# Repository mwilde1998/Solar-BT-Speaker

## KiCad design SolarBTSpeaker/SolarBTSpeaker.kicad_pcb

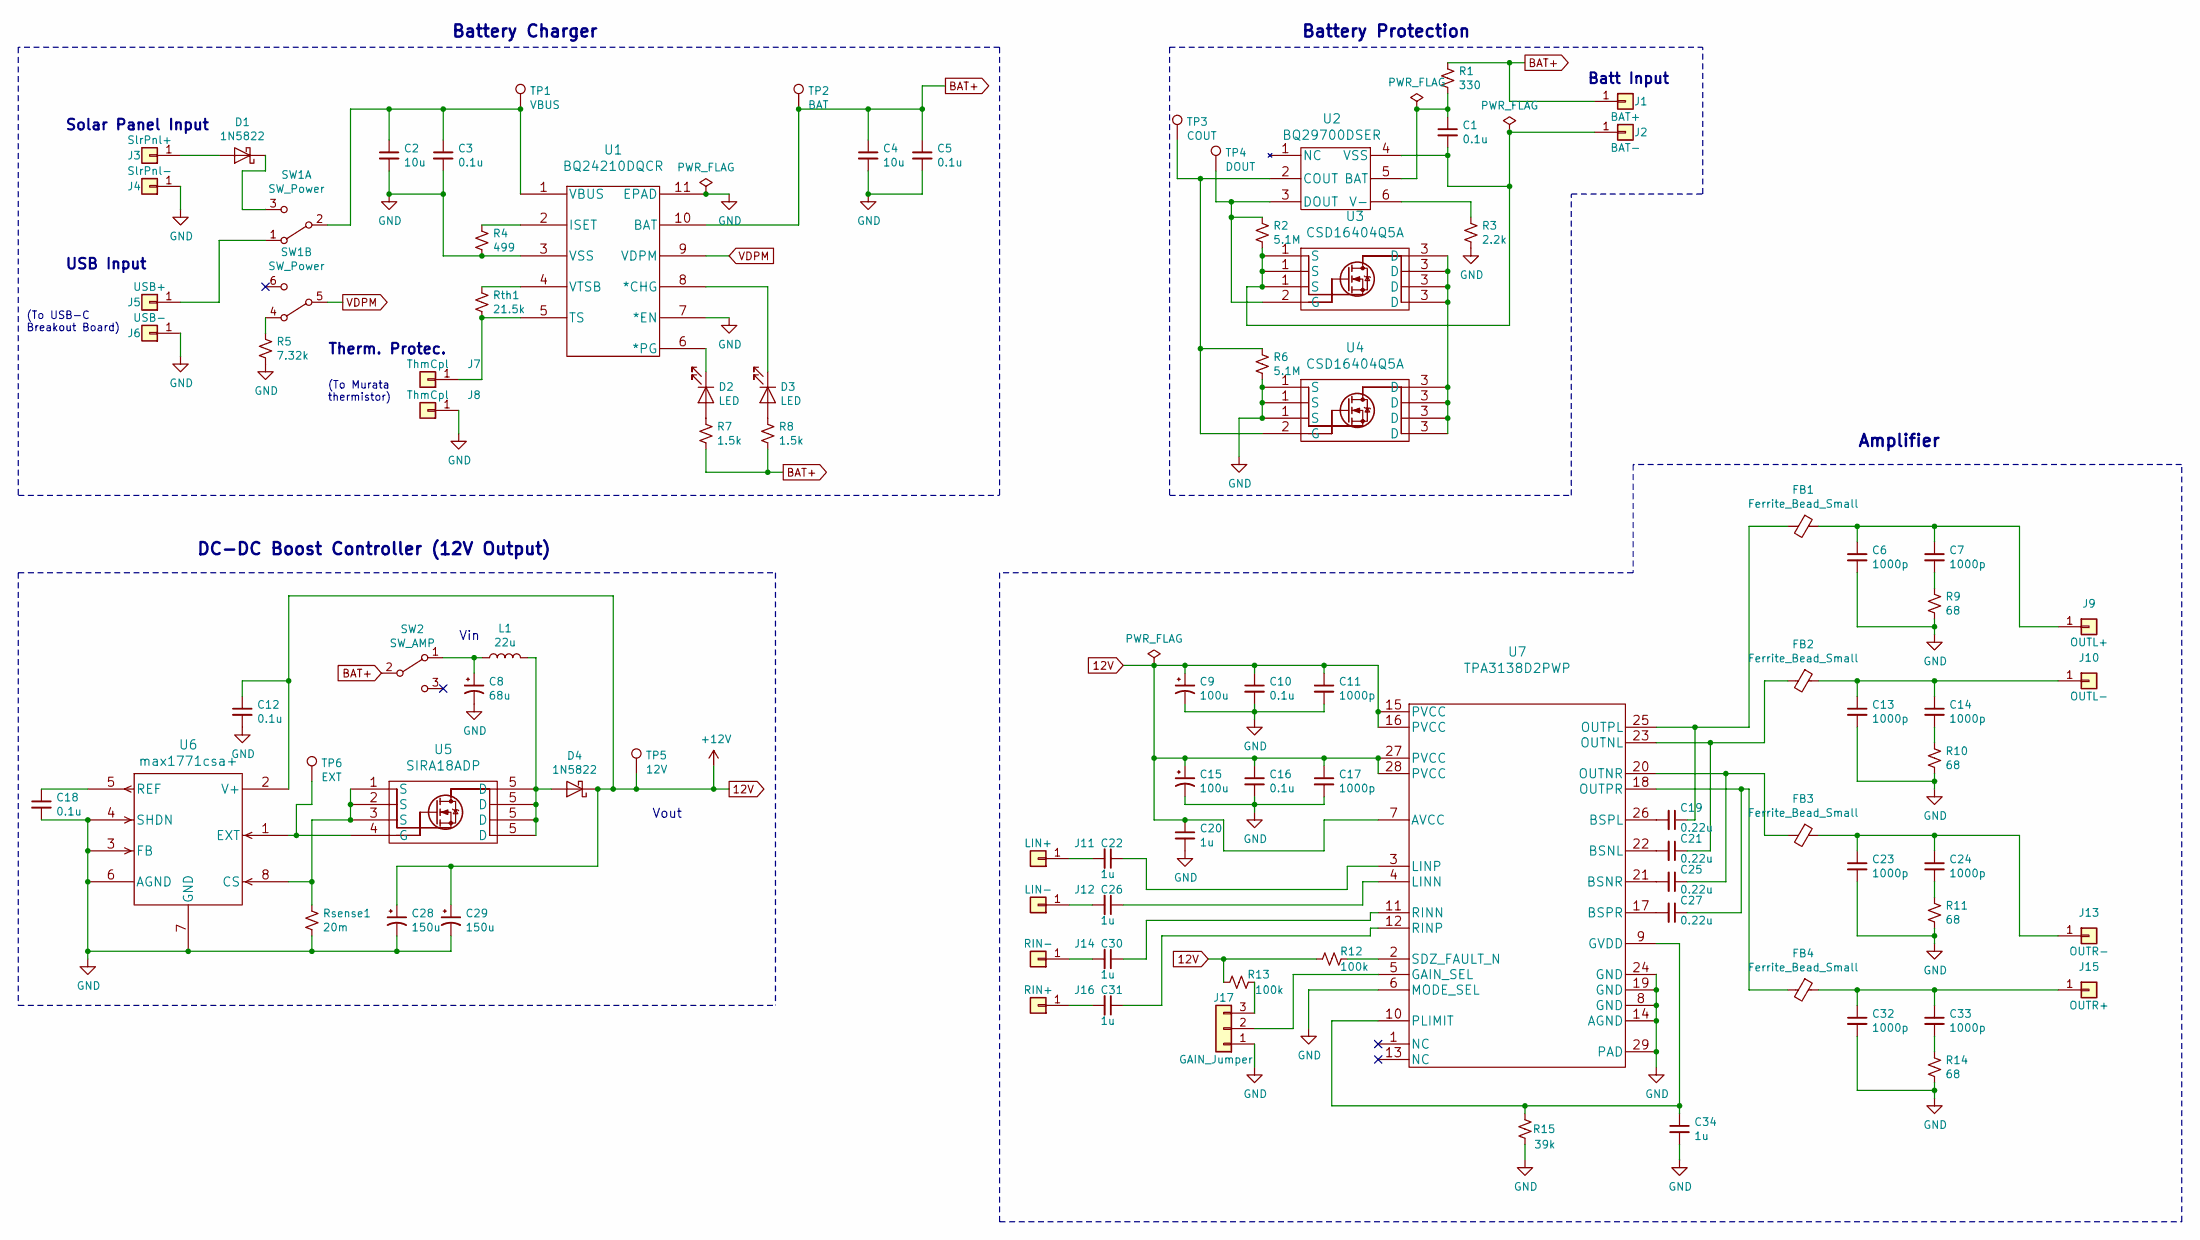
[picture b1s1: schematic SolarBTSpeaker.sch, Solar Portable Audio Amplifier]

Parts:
C1, C3, C5, C10, C12, C16, C18: 0.1u; C_0805_2012Metric_Pad1.15x1.40mm_HandSolder
C2, C4: 10u; C_0805_2012Metric_Pad1.15x1.40mm_HandSolder
C6, C7, C11, C13, C14, C17, C23, C24, C32, C33: 1000p; C_0805_2012Metric_Pad1.15x1.40mm_HandSolder
C8: 68u; CP_Radial_D6.3mm_P2.50mm
C9, C15: 100u; CP_Radial_D6.3mm_P2.50mm
C19, C21, C25, C27: 0.22u; C_0805_2012Metric_Pad1.15x1.40mm_HandSolder
C20, C22, C26, C30, C31, C34: 1u; C_0805_2012Metric_Pad1.15x1.40mm_HandSolder
C28, C29: 150u; CP_Radial_D6.3mm_P2.50mm
D1, D4: 1N5822; D_DO-201AD_P15.24mm_Horizontal
D2, D3: LED; LED_D3.0mm
FB1, FB2, FB3, FB4: Ferrite_Bead_Small; R_0805_2012Metric_Pad1.15x1.40mm_HandSolder
J1: BAT+; SolderWirePad_1x01_Drill1.5mm
J2: BAT-; SolderWirePad_1x01_Drill1.5mm
J3: SlrPnl+; SolderWirePad_1x01_Drill1.5mm
J4: SlrPnl-; SolderWirePad_1x01_Drill1.5mm
J5: USB+; SolderWirePad_1x01_Drill1.5mm
J6: USB-; SolderWirePad_1x01_Drill1.5mm
J7, J8: ThmCpl; SolderWirePad_1x01_Drill1.5mm
J9: OUTL+; SolderWirePad_1x01_Drill1.5mm
J10: OUTL-; SolderWirePad_1x01_Drill1.5mm
J11: LIN+; SolderWirePad_1x01_Drill1.5mm
J12: LIN-; SolderWirePad_1x01_Drill1.5mm
J13: OUTR-; SolderWirePad_1x01_Drill1.5mm
J14: RIN-; SolderWirePad_1x01_Drill1.5mm
J15: OUTR+; SolderWirePad_1x01_Drill1.5mm
J16: RIN+; SolderWirePad_1x01_Drill1.5mm
J17: GAIN_Jumper; PinSocket_1x03_P2.54mm_Vertical
L1: 22u; L_Radial_D14.8mm_P12mm_Wurth
R1: 330; R_0805_2012Metric_Pad1.15x1.40mm_HandSolder
R2, R6: 5.1M; R_0805_2012Metric_Pad1.15x1.40mm_HandSolder
R3: 2.2k; R_0805_2012Metric_Pad1.15x1.40mm_HandSolder
R4: 499; R_0805_2012Metric_Pad1.15x1.40mm_HandSolder
R5: 7.32k; R_0805_2012Metric_Pad1.15x1.40mm_HandSolder
R7, R8: 1.5k; R_0805_2012Metric_Pad1.15x1.40mm_HandSolder
R9, R10, R11, R14: 68; R_0805_2012Metric_Pad1.15x1.40mm_HandSolder
R12, R13: 100k; R_0805_2012Metric_Pad1.15x1.40mm_HandSolder
R15: 39k; R_0805_2012Metric_Pad1.15x1.40mm_HandSolder
Rsense1: 20m; R_0805_2012Metric_Pad1.15x1.40mm_HandSolder
Rth1: 21.5k; R_0805_2012Metric_Pad1.15x1.40mm_HandSolder
SW1: SW_Power; SW_CuK_JS202011CQN_DPDT_Straight
SW2: SW_AMP; PinSocket_1x03_P2.54mm_Vertical
TP1: VBUS; TestPoint_Pad_D1.5mm
TP2: BAT; TestPoint_Pad_D1.5mm
TP3: COUT; TestPoint_Pad_D1.5mm
TP4: DOUT; TestPoint_Pad_D1.5mm
TP5: 12V; TestPoint_Pad_D1.5mm
TP6: EXT; TestPoint_Pad_D1.5mm
U1: BQ24210DQCR; WSON-10-1EP_2x3mm_P0.5mm_EP0.84x2.4mm
U2: BQ29700DSER; WSON-6_1.5x1.5mm_P0.5mm
U3, U4: CSD16404Q5A; VSONP-8-1EP_5x6_P1.27mm
U5: SIRA18ADP; PowerPAK_SO-8_Single
U6: max1771csa+; SOIC-8_3.9x4.9mm_P1.27mm
U7: TPA3138D2PWP; HTSSOP-28-1EP_4.4x9.7mm_P0.65mm_EP2.85x5.4mm

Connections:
12V: C9.1, C10.1, C11.1, C12.1, C15.1, C16.1, C17.1, C20.1, C28.1, C29.1, D4.1 (K), R12.2, R13.2, TP5.1, U6.2 (V+), U7.7 (AVCC), U7.15 (PVCC), U7.16 (PVCC), U7.27 (PVCC), U7.28 (PVCC)
BAT+: C4.1, C5.1, J1.1, R1.1, R7.2, R8.2, SW2.2 (B), TP2.1, U1.10 (BAT)
GND: C2.2, C3.2, C4.2, C5.2, C6.2, C8.2, C9.2, C10.2, C11.2, C12.2, C13.2, C15.2, C16.2, C17.2, C18.2, C20.2, C23.2, C28.2, C29.2, C32.2, C34.2, J4.1, J6.1, J8.1, J17.1, R3.2, R4.2, R5.2, R6.2, R9.2, R10.2, R11.2, R14.2, R15.1, Rsense1.2, U1.3 (VSS), U1.7 (*EN), U1.11 (EPAD), U4.1 (S), U6.3 (FB), U6.4 (SHDN), U6.6 (AGND), U6.7 (GND), U7.6 (MODE_SEL), U7.8 (GND), U7.14 (AGND), U7.19 (GND), U7.24 (GND), U7.29 (PAD); also elsewhere on the board
unnamed: C1.1, R1.2, U2.5 (BAT)
unnamed: C1.2, J2.1, R2.2, U2.4 (VSS), U3.1 (S)
unnamed: C2.1, C3.1, SW1.2 (B), TP1.1, U1.1 (VBUS)
unnamed: C6.1, C7.1, FB1.1, J9.1
unnamed: C7.2, R9.1
unnamed: C8.1, L1.1, SW2.1 (A)
unnamed: C13.1, C14.1, FB2.1, J10.1
unnamed: C14.2, R10.1
unnamed: C18.1, U6.5 (REF)
unnamed: C19.1, FB1.2, U7.25 (OUTPL)
unnamed: C19.2, U7.26 (BSPL)
unnamed: C21.1, FB2.2, U7.23 (OUTNL)
unnamed: C21.2, U7.22 (BSNL)
unnamed: C22.1, U7.3 (LINP)
unnamed: C22.2, J11.1
unnamed: C23.1, C24.1, FB3.1, J13.1
unnamed: C24.2, R11.1
unnamed: C25.1, FB3.2, U7.20 (OUTNR)
unnamed: C25.2, U7.21 (BSNR)
unnamed: C26.1, U7.4 (LINN)
unnamed: C26.2, J12.1
unnamed: C27.1, FB4.2, U7.18 (OUTPR)
unnamed: C27.2, U7.17 (BSPR)
unnamed: C30.1, U7.11 (RINN)
unnamed: C30.2, J14.1
unnamed: C31.1, U7.12 (RINP)
unnamed: C31.2, J16.1
unnamed: C32.1, C33.1, FB4.1, J15.1
unnamed: C33.2, R14.1
unnamed: C34.1, R15.2, U7.9 (GVDD), U7.10 (PLIMIT)
unnamed: D1.1 (K), SW1.3 (C)
unnamed: D1.2 (A), J3.1
unnamed: D2.1 (K), U1.6 (*PG)
unnamed: D2.2 (A), R7.1
unnamed: D3.1 (K), U1.8 (*CHG)
unnamed: D3.2 (A), R8.1
unnamed: D4.2 (A), L1.2, U5.5 (D)
unnamed: J5.1, SW1.1 (A)
unnamed: J7.1, Rth1.2, U1.5 (TS)
unnamed: J17.2, U7.5 (GAIN_SEL)
unnamed: J17.3, R13.1
unnamed: R2.1, TP4.1, U2.3 (DOUT), U3.2 (G)
unnamed: R3.1, U2.6 (V-)
unnamed: R4.1, U1.2 (ISET)
unnamed: R5.1, SW1.4 (A)
unnamed: R6.1, TP3.1, U2.2 (COUT), U4.2 (G)
unnamed: R12.1, U7.2 (SDZ_FAULT_N)
unnamed: Rsense1.1, U5.1 (S), U5.2 (S), U5.3 (S), U6.8 (CS)
unnamed: Rth1.1, U1.4 (VTSB)
unnamed: TP6.1, U5.4 (G), U6.1 (EXT)
unnamed: U3.3 (D), U4.3 (D)
VDPM: SW1.5 (B), U1.9 (VDPM)

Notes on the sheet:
Solar Panel Input
USB Input
(To USB-C Breakout Board)
(To Murata thermistor)
Therm. Protec.
Vin
Battery Charger
Battery Protection
Vout
DC-DC Boost Controller (12V Output)
Amplifier
Batt Input

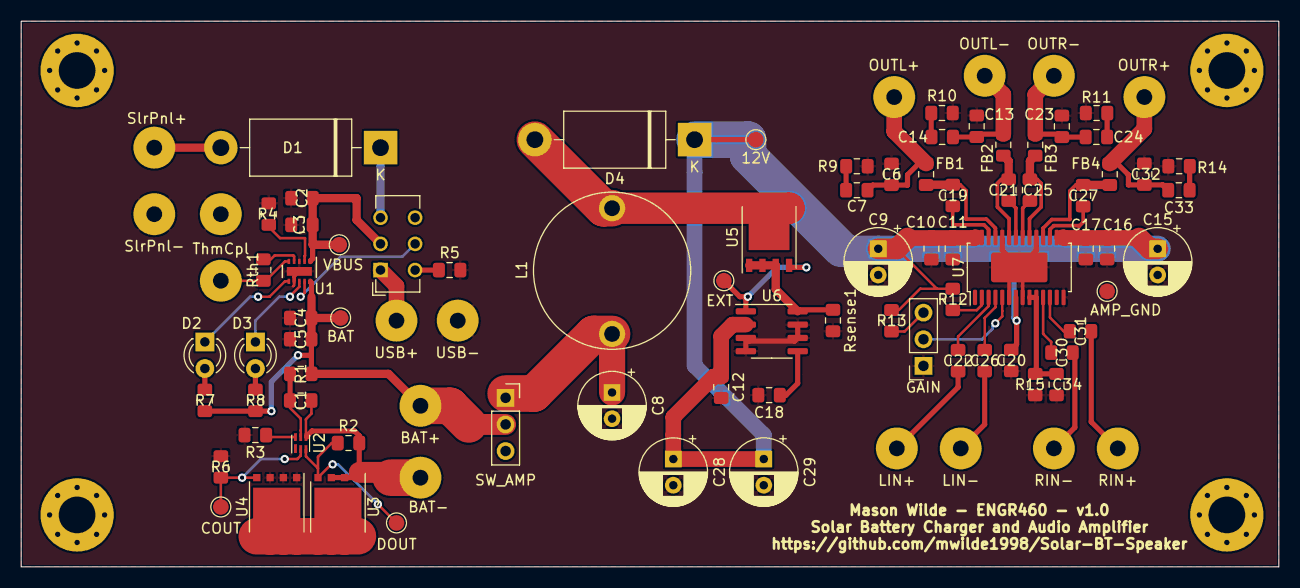
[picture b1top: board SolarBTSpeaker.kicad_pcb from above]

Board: 2 copper layers, 120.0 x 52.1 mm, 93 parts (0 on the bottom side), 55 nets.

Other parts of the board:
TP7: AMP_GND; TestPoint_Pad_D1.5mm

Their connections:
GND: TP7.1; also elsewhere on the board

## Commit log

2020-04-22 Initial commit of new project files
2020-04-23 Schematic updated
2020-04-23 Minor schematic updates
2020-04-24 Schematic Update
2020-04-24 Updated schematic with datasheets, fixed ERC warnings
2020-04-26 PCB and schematic significantly updated
2020-04-26 PCB updated, ground fills added
2020-04-26 Schematic and PCB finalized, gerbers and drill plot created
2020-05-03 PCB, schematic, and silkscreen references finalized
2020-06-11 Small change to .pro file
2020-06-11 Added a few images to be used for documentation
2020-06-11 Additional images for documentation purposes
2020-06-11 Added Image of Schematic
2020-06-11 Added screenshot of PCB design
2020-06-11 Added 3D render of PCB
2020-06-11 Added image of thermistor circuit
2020-06-11 Fixed a cursor that had accidentally made it into the screenshot
2020-06-11 BOMs and video of amplifier operating added
